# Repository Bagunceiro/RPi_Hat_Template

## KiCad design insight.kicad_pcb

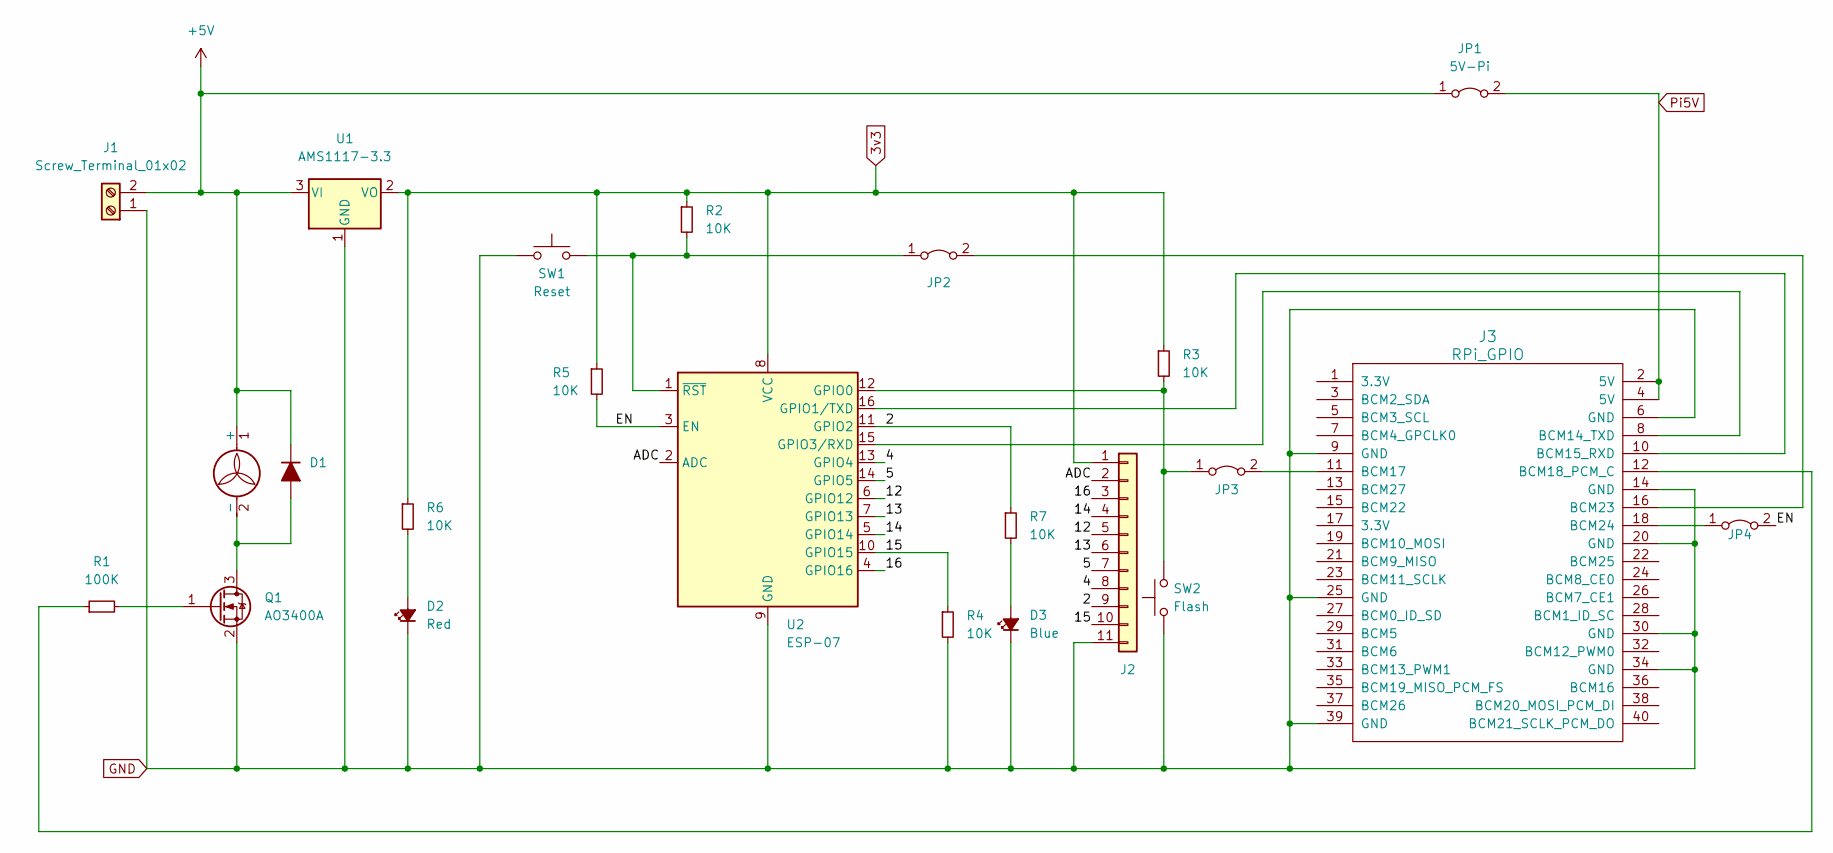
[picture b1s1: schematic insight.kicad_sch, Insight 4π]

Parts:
D1: 1N4007; D_0805_2012Metric
D2: Red; D_0805_2012Metric
D3: Blue; D_0805_2012Metric
J1: Screw_Terminal_01x02; TerminalBlock_bornier-2_P5.08mm
J2: ESP IO; PinHeader_1x11_P2.54mm_Vertical
J3: RPi_GPIO; PinHeader_2x20_P2.54mm_Vertical
JP1: 5V-Pi; PinHeader_1x02_P2.54mm_Vertical
JP2, JP3, JP4: Jumper_2_Bridged; SolderJumper-2_P1.3mm_Bridged2Bar_RoundedPad1.0x1.5mm
M1: Fan; PinHeader_1x02_P2.54mm_Vertical
Q1: AO3400A; SOT-23
R1: 100K; R_0805_2012Metric
R2, R3, R4, R5, R6, R7: 10K; R_0805_2012Metric
SW1: Reset; SW_PUSH_6mm
SW2: Flash; SW_PUSH_6mm
U1: AMS1117-3.3; SOT-223-3_TabPin2
U2: ESP-07

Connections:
3v3: J2.1, R2.1, R3.1, R5.1, R6.1, U1.2 (VO), U2.8 (VCC)
+5V: D1.1 (K), J1.2, JP1.1 (A), M1.1 (+), U1.3 (VI)
/2: J2.9, R7.1, U2.11 (GPIO2)
/4: J2.8, U2.13 (GPIO4)
/5: J2.7, U2.14 (GPIO5)
/12: J2.5, U2.6 (GPIO12)
/13: J2.6, U2.7 (GPIO13)
/14: J2.4, U2.5 (GPIO14)
/15: J2.10, R4.1, U2.10 (GPIO15)
/16: J2.3, U2.4 (GPIO16)
/ADC: J2.2, U2.2 (ADC)
/EN: JP4.2 (B), R5.2, U2.3 (EN)
GND: D2.1 (K), D3.1 (K), J1.1, J2.11, J3.6 (GND), J3.9 (GND), J3.14 (GND), J3.20 (GND), J3.25 (GND), J3.30 (GND), J3.34 (GND), J3.39 (GND), Q1.2 (S), R4.2, SW1.1, SW2.1, U1.1 (GND), U2.9 (GND)
unnamed: D1.2 (A), M1.2 (-), Q1.3 (D)
unnamed: D2.2 (A), R6.2
unnamed: D3.2 (A), R7.2
unnamed: J3.8 (BCM14_TXD), U2.15 (GPIO3/RXD)
unnamed: J3.10 (BCM15_RXD), U2.16 (GPIO1/TXD)
unnamed: J3.11 (BCM17), JP3.2 (B)
unnamed: J3.12 (BCM18_PCM_C), R1.1
unnamed: J3.16 (BCM23), JP2.2 (B)
unnamed: J3.18 (BCM24), JP4.1 (A)
unnamed: JP2.1 (A), R2.2, SW1.2, U2.1 (~RST)
unnamed: JP3.1 (A), R3.2, SW2.2, U2.12 (GPIO0)
unnamed: Q1.1 (G), R1.2
Pi5V: J3.2 (5V), J3.4 (5V), JP1.2 (B)

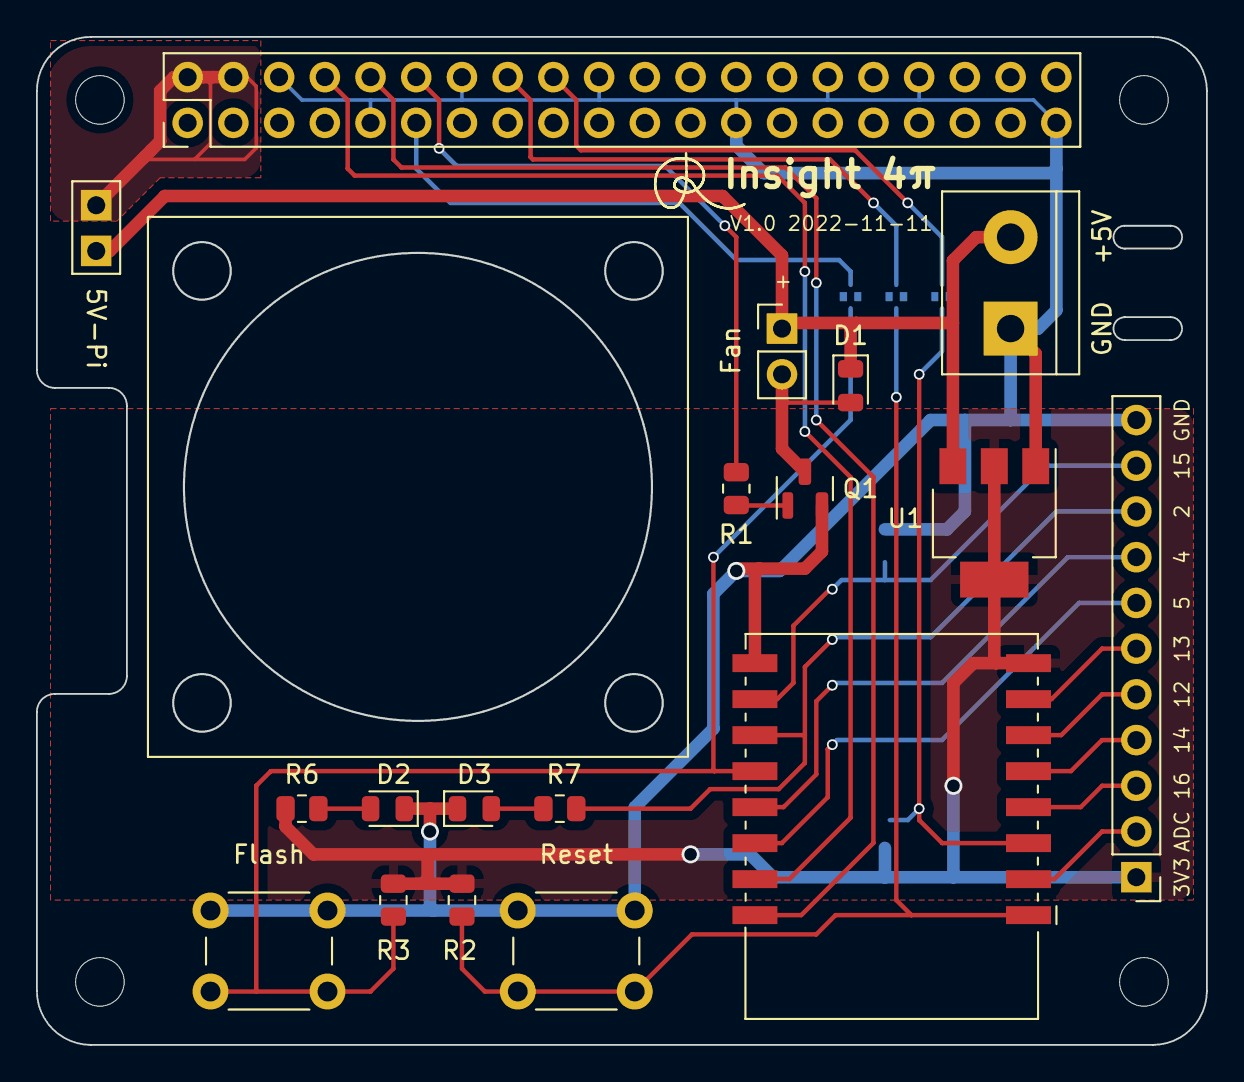
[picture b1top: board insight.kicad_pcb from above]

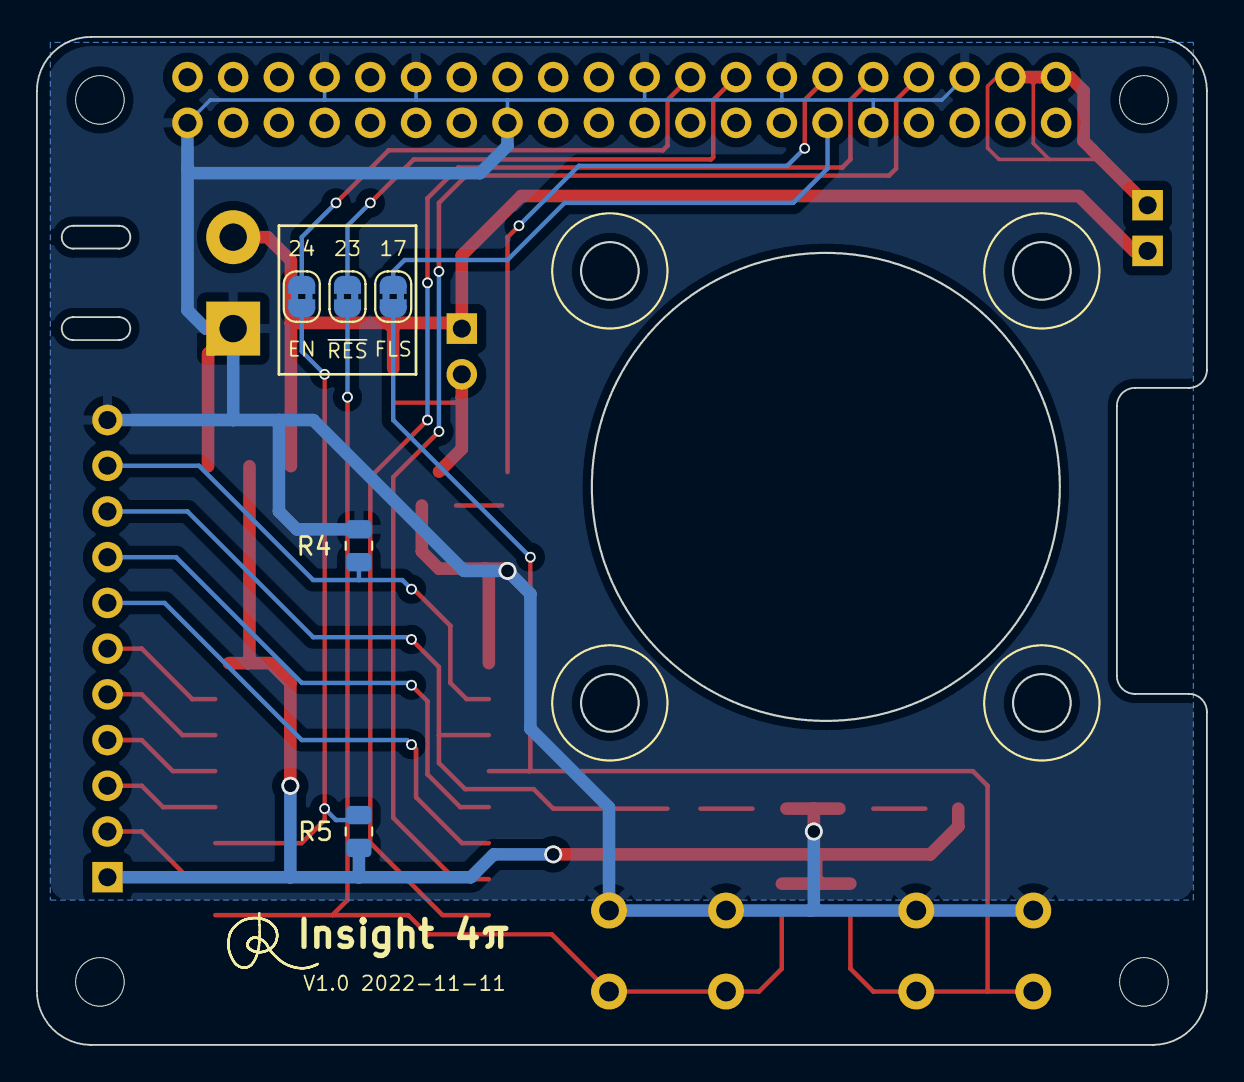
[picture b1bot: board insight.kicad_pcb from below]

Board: 2 copper layers, 65.0 x 56.0 mm, 23 parts (5 on the bottom side), 26 nets.

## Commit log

2022-12-10 clear out crud
